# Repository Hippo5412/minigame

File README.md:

# minigame

A *mini,* one handed, 29 key (soldered) keyboard made for *gaming* with all the keys you need :)

Firmware:
https://github.com/Hippo5412/qmk_firmware

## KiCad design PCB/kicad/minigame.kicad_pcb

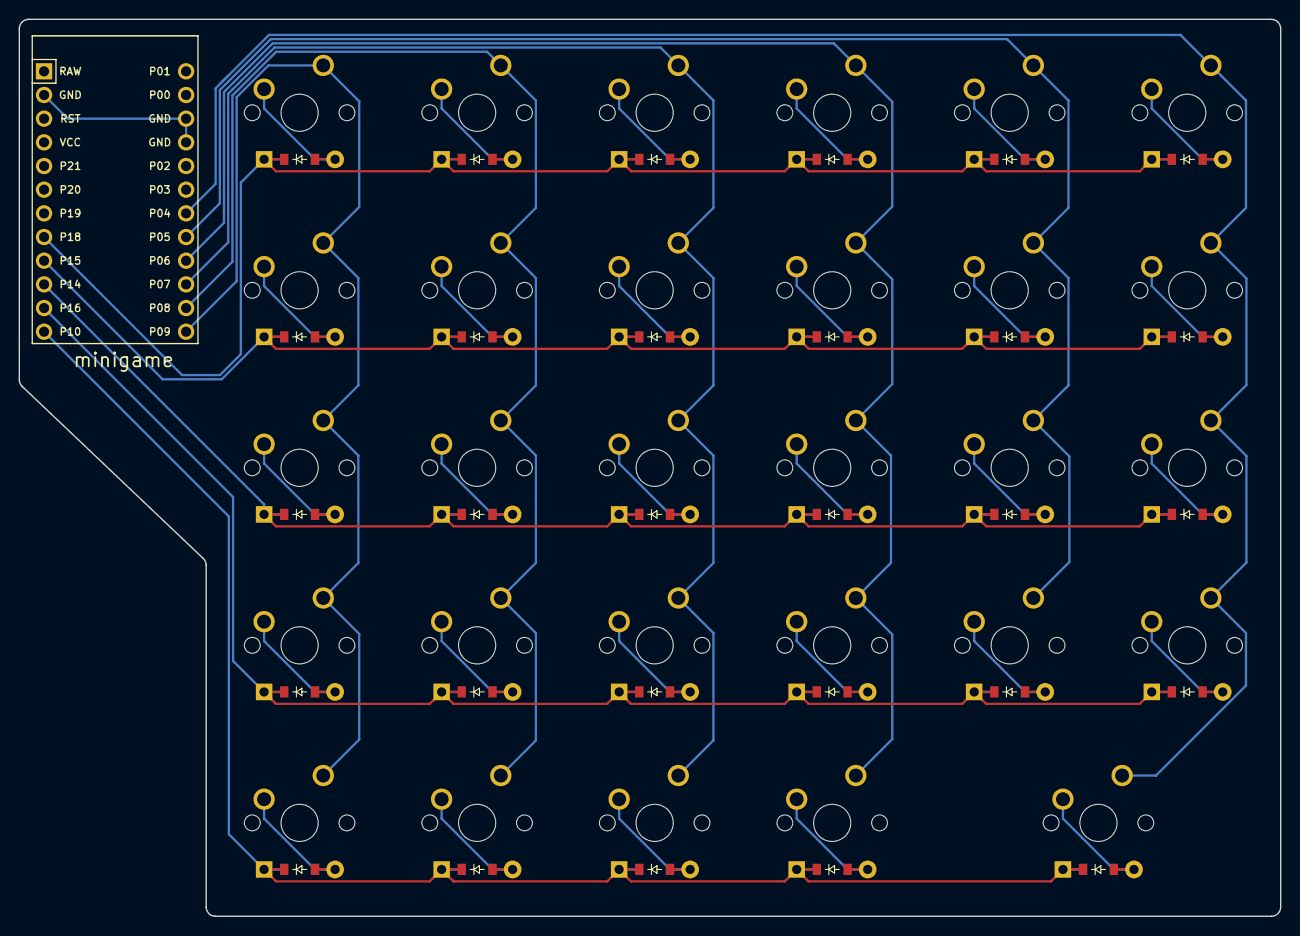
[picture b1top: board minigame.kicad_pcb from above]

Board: 2 copper layers, 135.4 x 96.2 mm, 59 parts (0 on the bottom side), 41 nets.

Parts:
D1, D2, D3, D4, D5, D6, D7, D8, D9, D10, D11, D12, D13, D14, D15, D16, D17, D18, D19, D20, D21, D22, D23, D24, D25, D26, D27, D28, D29: ComboDiode
MCU1: ProMicro
S1, S2, S3, S4, S5, S6, S7, S8, S9, S10, S11, S12, S13, S14, S15, S16, S17, S18, S19, S20, S21, S22, S23, S24, S25, S26, S27, S28, S29: MX

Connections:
GND: MCU1.2, MCU1.15, MCU1.16
P4: MCU1.19, S25.1, S26.1, S27.1, S28.1, S29.1
P5: MCU1.20, S21.1, S22.1, S23.1, S24.1
P6: MCU1.21, S16.1, S17.1, S18.1, S19.1, S20.1
P7: MCU1.22, S11.1, S12.1, S13.1, S14.1, S15.1
P8: MCU1.23, S6.1, S7.1, S8.1, S9.1, S10.1
P9: MCU1.24, S1.1, S2.1, S3.1, S4.1, S5.1
P10: D1.1, D6.1, D11.1, D16.1, D25.1, MCU1.12
P14: D3.1, D8.1, D13.1, D18.1, D22.1, D27.1, MCU1.10
P15: D4.1, D9.1, D14.1, D19.1, D23.1, D28.1, MCU1.9
P16: D2.1, D7.1, D12.1, D17.1, D21.1, D26.1, MCU1.11
P18: D5.1, D10.1, D15.1, D20.1, D24.1, D29.1, MCU1.8
index_bottom: D21.2, S21.2
index_home: D22.2, S22.2
index_num: D24.2, S24.2
index_top: D23.2, S23.2
inner_bottom: D26.2, S26.2
inner_home: D27.2, S27.2
inner_mod: D25.2, S25.2
inner_num: D29.2, S29.2
inner_top: D28.2, S28.2
middle_bottom: D17.2, S17.2
middle_home: D18.2, S18.2
middle_mod: D16.2, S16.2
middle_num: D20.2, S20.2
middle_top: D19.2, S19.2
outer_bottom: D2.2, S2.2
outer_home: D3.2, S3.2
outer_mod: D1.2, S1.2
outer_num: D5.2, S5.2
outer_top: D4.2, S4.2
pinky_bottom: D7.2, S7.2
pinky_home: D8.2, S8.2
pinky_mod: D6.2, S6.2
pinky_num: D10.2, S10.2
pinky_top: D9.2, S9.2
ring_bottom: D12.2, S12.2
ring_home: D13.2, S13.2
ring_mod: D11.2, S11.2
ring_num: D15.2, S15.2
ring_top: D14.2, S14.2

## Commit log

2025-10-26 Update description of the minigame keyboard
2025-10-26 Emphasize 'gaming' in README description
2025-10-26 Added PCB and ergogen files
2025-10-26 Add firmware link to README
    Added firmware link to README.
2025-11-01 added images
2025-11-01 Add keyboard image to README
    Added an image of the keyboard to the README.
2025-11-01 Add GNU General Public License v3
